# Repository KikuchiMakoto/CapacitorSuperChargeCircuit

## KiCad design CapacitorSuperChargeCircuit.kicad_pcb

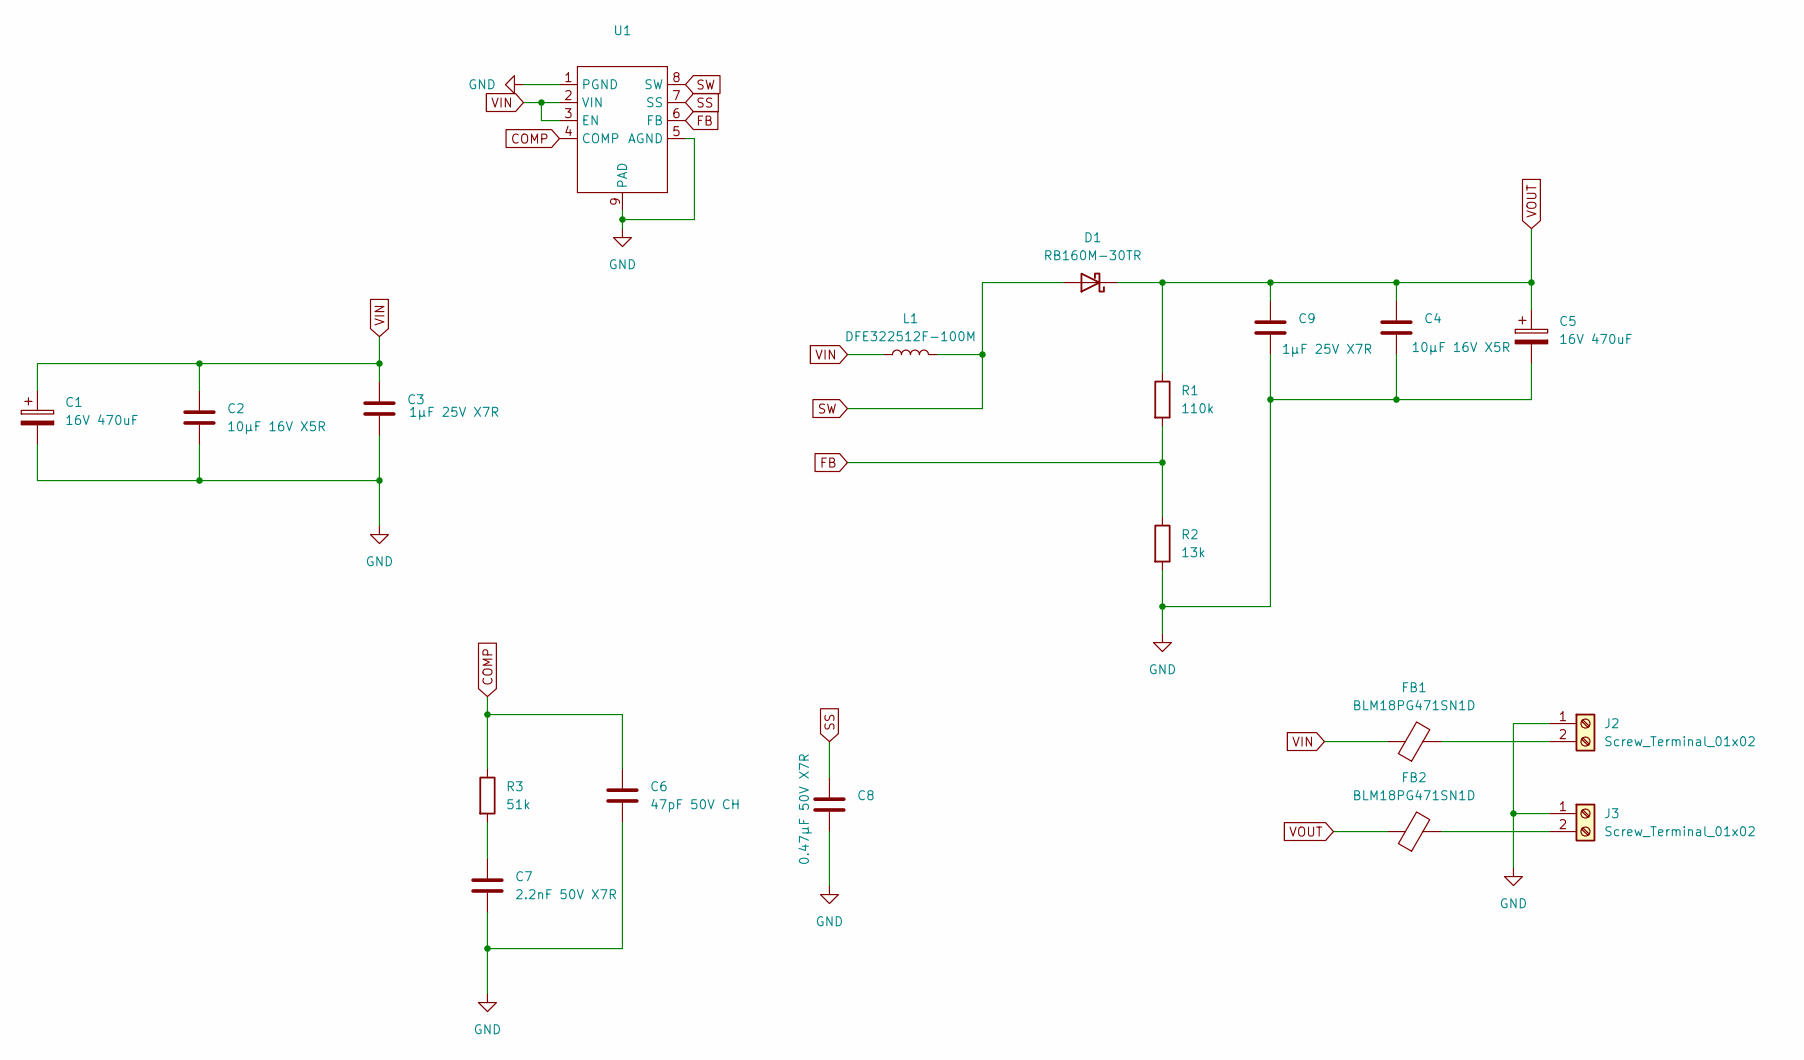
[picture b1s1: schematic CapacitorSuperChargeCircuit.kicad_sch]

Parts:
C1, C5: 16V 470uF; CP_Radial_D8.0mm_P3.50mm
C2, C4: 10μF 16V X5R; C_0603_1608Metric_Pad1.08x0.95mm_HandSolder
C3, C9: 1μF 25V X7R; C_0603_1608Metric_Pad1.08x0.95mm_HandSolder
C6: 47pF 50V CH; C_0603_1608Metric_Pad1.08x0.95mm_HandSolder
C7: 2.2nF 50V X7R; C_0603_1608Metric_Pad1.08x0.95mm_HandSolder
C8: 0.47μF 50V X7R; C_0603_1608Metric_Pad1.08x0.95mm_HandSolder
D1: RB160M-30TR; D_SOD-123
FB1, FB2: BLM18PG471SN1D; L_0603_1608Metric
J2, J3: Screw_Terminal_01x02; TerminalBlock_bornier-2_P5.08mm
L1: DFE322512F-100M; L_1210_3225Metric_Pad1.42x2.65mm_HandSolder
R1: 110k; R_0603_1608Metric_Pad0.98x0.95mm_HandSolder
R2: 13k; R_0603_1608Metric_Pad0.98x0.95mm_HandSolder
R3: 51k; R_0603_1608Metric_Pad0.98x0.95mm_HandSolder
U1: PAM242x

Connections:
COMP: C6.1, R3.1, U1.4 (COMP)
FB: R1.2, R2.1, U1.6 (FB)
GND: C1.2, C2.2, C3.2, C4.2, C5.2, C6.2, C7.2, C8.2, C9.2, J2.1, J3.1, R2.2, U1.1 (PGND), U1.5 (AGND), U1.9 (PAD)
unnamed: C7.1, R3.2
unnamed: FB1.2, J2.2
unnamed: FB2.2, J3.2
SS: C8.1, U1.7 (SS)
SW: D1.2 (A), L1.2, U1.8 (SW)
VIN: C1.1, C2.1, C3.1, FB1.1, L1.1, U1.2 (VIN), U1.3 (EN)
VOUT: C4.1, C5.1, C9.1, D1.1 (K), FB2.1, R1.1

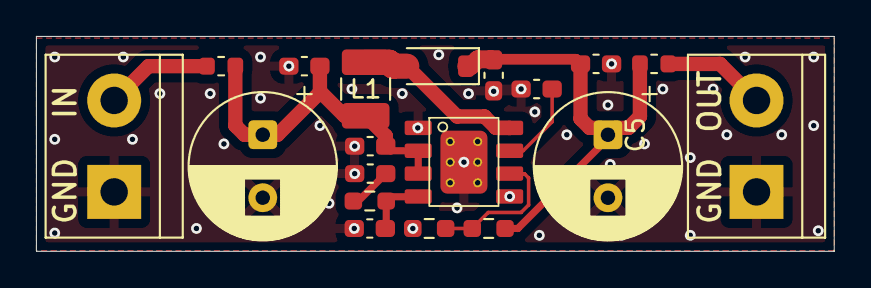
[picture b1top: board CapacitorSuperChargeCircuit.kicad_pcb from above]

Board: 2 copper layers, 44.3 x 11.9 mm, 19 parts (0 on the bottom side), 10 nets.

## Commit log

2025-09-10 v2 smd version
2025-09-10 v2 smd version foxed
2025-09-15 add thumbnail
